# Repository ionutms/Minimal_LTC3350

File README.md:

# Minimal_LTC3350

## Overview

This repository contains a minimal KiCad design project for the Analog Devices LTC3350, a high-current supercapacitor backup controller and system monitor. The project includes schematic designs and PCB layout files for implementing this versatile backup power solution.

## Disclaimer

> [!NOTE]
> This project is provided "as is" and without any warranty, express or implied. For more details, please see the [LICENSE](LICENSE) file.

## About the LTC3350

The LTC3350 from Analog Devices is a high-current supercapacitor backup controller and system monitor designed for high-reliability backup power applications. It integrates a synchronous step-down/step-up controller that charges and monitors a series stack of 1–4 supercapacitors.

Key features include:

- **High-Efficiency Power Conversion:**
  - Synchronous step-down CC/CV charging for 1–4 series supercapacitors
  - Step-up mode in backup for greater utilization of stored energy
  - Supports 10A+ charge and backup currents
- **Advanced Monitoring:**
  - 14-bit ADC for monitoring system voltages and currents
  - Capacitance and ESR monitoring
  - I²C/SMBus interface for reading monitored parameters
- **Protection Features:**
  - Active overvoltage protection shunts
  - Internal active balancers (no external balance resistors needed)
  - Dual ideal diode PowerPath™ controller with N-channel MOSFETs
- **Programmable Current Limit:** Prioritizes system load over capacitor charge current
- **Wide Operating Range:**
  - Input Voltage (VIN): 4.5V to 35V
  - Capacitor Voltage (VCAP): Up to 5V per capacitor
- **Package:** Available in a 38-lead QFN package (5mm × 7mm × 0.75mm) with exposed pad
- **Automotive Qualified:** AEC-Q100 qualified for automotive applications

## Project Structure

```
minimal_ltc3350/
├── minimal_ltc3350.kicad_pro                     # Project configuration file
├── minimal_ltc3350.kicad_sch                     # Main schematic file
├── minimal_ltc3350.kicad_pcb                     # PCB layout file
├── fp-lib-table                                  # Footprint library table
├── sym-lib-table                                 # Symbol library table
├── docs/                                         # Documentation files
│   ├── bom/                                      # Bill of Materials
│   │   └── minimal_ltc3350_ibom.html             # Interactive BOM file
│   ├── pictures/                                 # Images and photos
│   │   ├── 1_minimal_ltc3350_side.png            # Side view of PCB
│   │   ├── 2_minimal_ltc3350_top.png             # Top view of PCB
│   │   └── 3_minimal_ltc3350_bottom.png          # Bottom view of PCB
│   └── schematics/                               # Schematic PDF exports
│       └── minimal_ltc3350_schematics.pdf        # Complete schematics PDF
└── KiCAD_Symbols_Generator/                      # Submodule for symbol generation from CSV data
```

## Project Features

This design provides a minimal implementation of the LTC3350 with:

- Proper power supply connections for 4.5V to 35V input range
- Supercapacitor stack configuration (1–4 series capacitors)
- Active balancing circuitry
- I²C/SMBus communication interface
- Current sensing and monitoring
- Standard footprint for the 38-lead QFN package

## Getting Started

### Prerequisites

- [KiCad EDA](https://www.kicad.org/) version 9.0 or later installed on your system
- Git (for cloning the repository and submodule management)

### Opening the Project

1. **Clone the repository** (including submodules):
   ```bash
   git clone --recursive https://github.com/ionutms/Minimal_LTC3350.git
   ```

   If you've already cloned the repository without submodules, initialize them with:
   ```bash
   git submodule init
   git submodule update
   ```

2. **Open the project in KiCad**:
   - Launch KiCad
   - Click "Open Existing Project"
   - Navigate to the cloned repository folder
   - Select the `minimal_ltc3350.kicad_pro` file

3. **Explore the design**:
   - Open the schematic editor to view the circuit design
   - Open the PCB editor to view the board layout
   - Review the symbol and footprint libraries used in the design

### Project Files

- **Main schematic**: `minimal_ltc3350.kicad_sch` - Contains the primary circuit design with the LTC3350 and support components
- **PCB layout**: `minimal_ltc3350.kicad_pcb` - Physical board design file with proper component placement
- **Project configuration**: `minimal_ltc3350.kicad_pro` - KiCad project settings

## Dependencies

This project has the following dependencies:

### 1. KiCAD Symbols Generator

This repository uses [KiCAD_Symbols_Generator](https://github.com/ionutms/KiCAD_Symbols_Generator) as a submodule for custom symbol generation.

To initialize the submodule after cloning this repository:

```bash
git submodule update --init --recursive
```

### 2. 3D Models

This project requires the [3D_Models_Vault](https://github.com/ionutms/3D_Models_Vault) repository for 3D models.

#### Setup for KiCAD 9:

1. Clone the 3D models repository:
   ```bash
   git clone https://github.com/ionutms/3D_Models_Vault.git
   ```

2. In KiCAD 9, add an environment variable:
   - Variable name: `KICAD9_3D_MODELS_VAULT`
   - Variable value: Full path to where you cloned the 3D_Models_Vault repository

## Usage

After setting up the dependencies, open the project in KiCad 9 to access all features including the 3D models.

## Symbol Generator Submodule

This project includes the KiCAD_Symbols_Generator as a submodule, which provides tools for generating KiCad symbols from CSV data files. For more information on using this tool, see the [KiCAD_Symbols_Generator documentation](minimal_ltc3350/KiCAD_Symbols_Generator/README.md).

## Documentation

The `docs` folder contains:
- Schematic PDF exports
- Images and photos of the design

## Visuals

The following images showcase the PCB design from different perspectives:

*Top View of the PCB*

*Bottom View of the PCB*

*Side View of the PCB*

*Left View of the PCB*

*Right View of the PCB*

*Front View of the PCB*

*Back View of the PCB*

## License

This project is licensed under the MIT License - see the [LICENSE](LICENSE) file for details.

## References

- [LTC3350 Datasheet](https://www.analog.com/media/en/technical-documentation/data-sheets/ltc3350.pdf)
- [LTC3350 Product Page](https://www.analog.com/en/products/ltc3350.html)
- [KiCad EDA](https://www.kicad.org/)

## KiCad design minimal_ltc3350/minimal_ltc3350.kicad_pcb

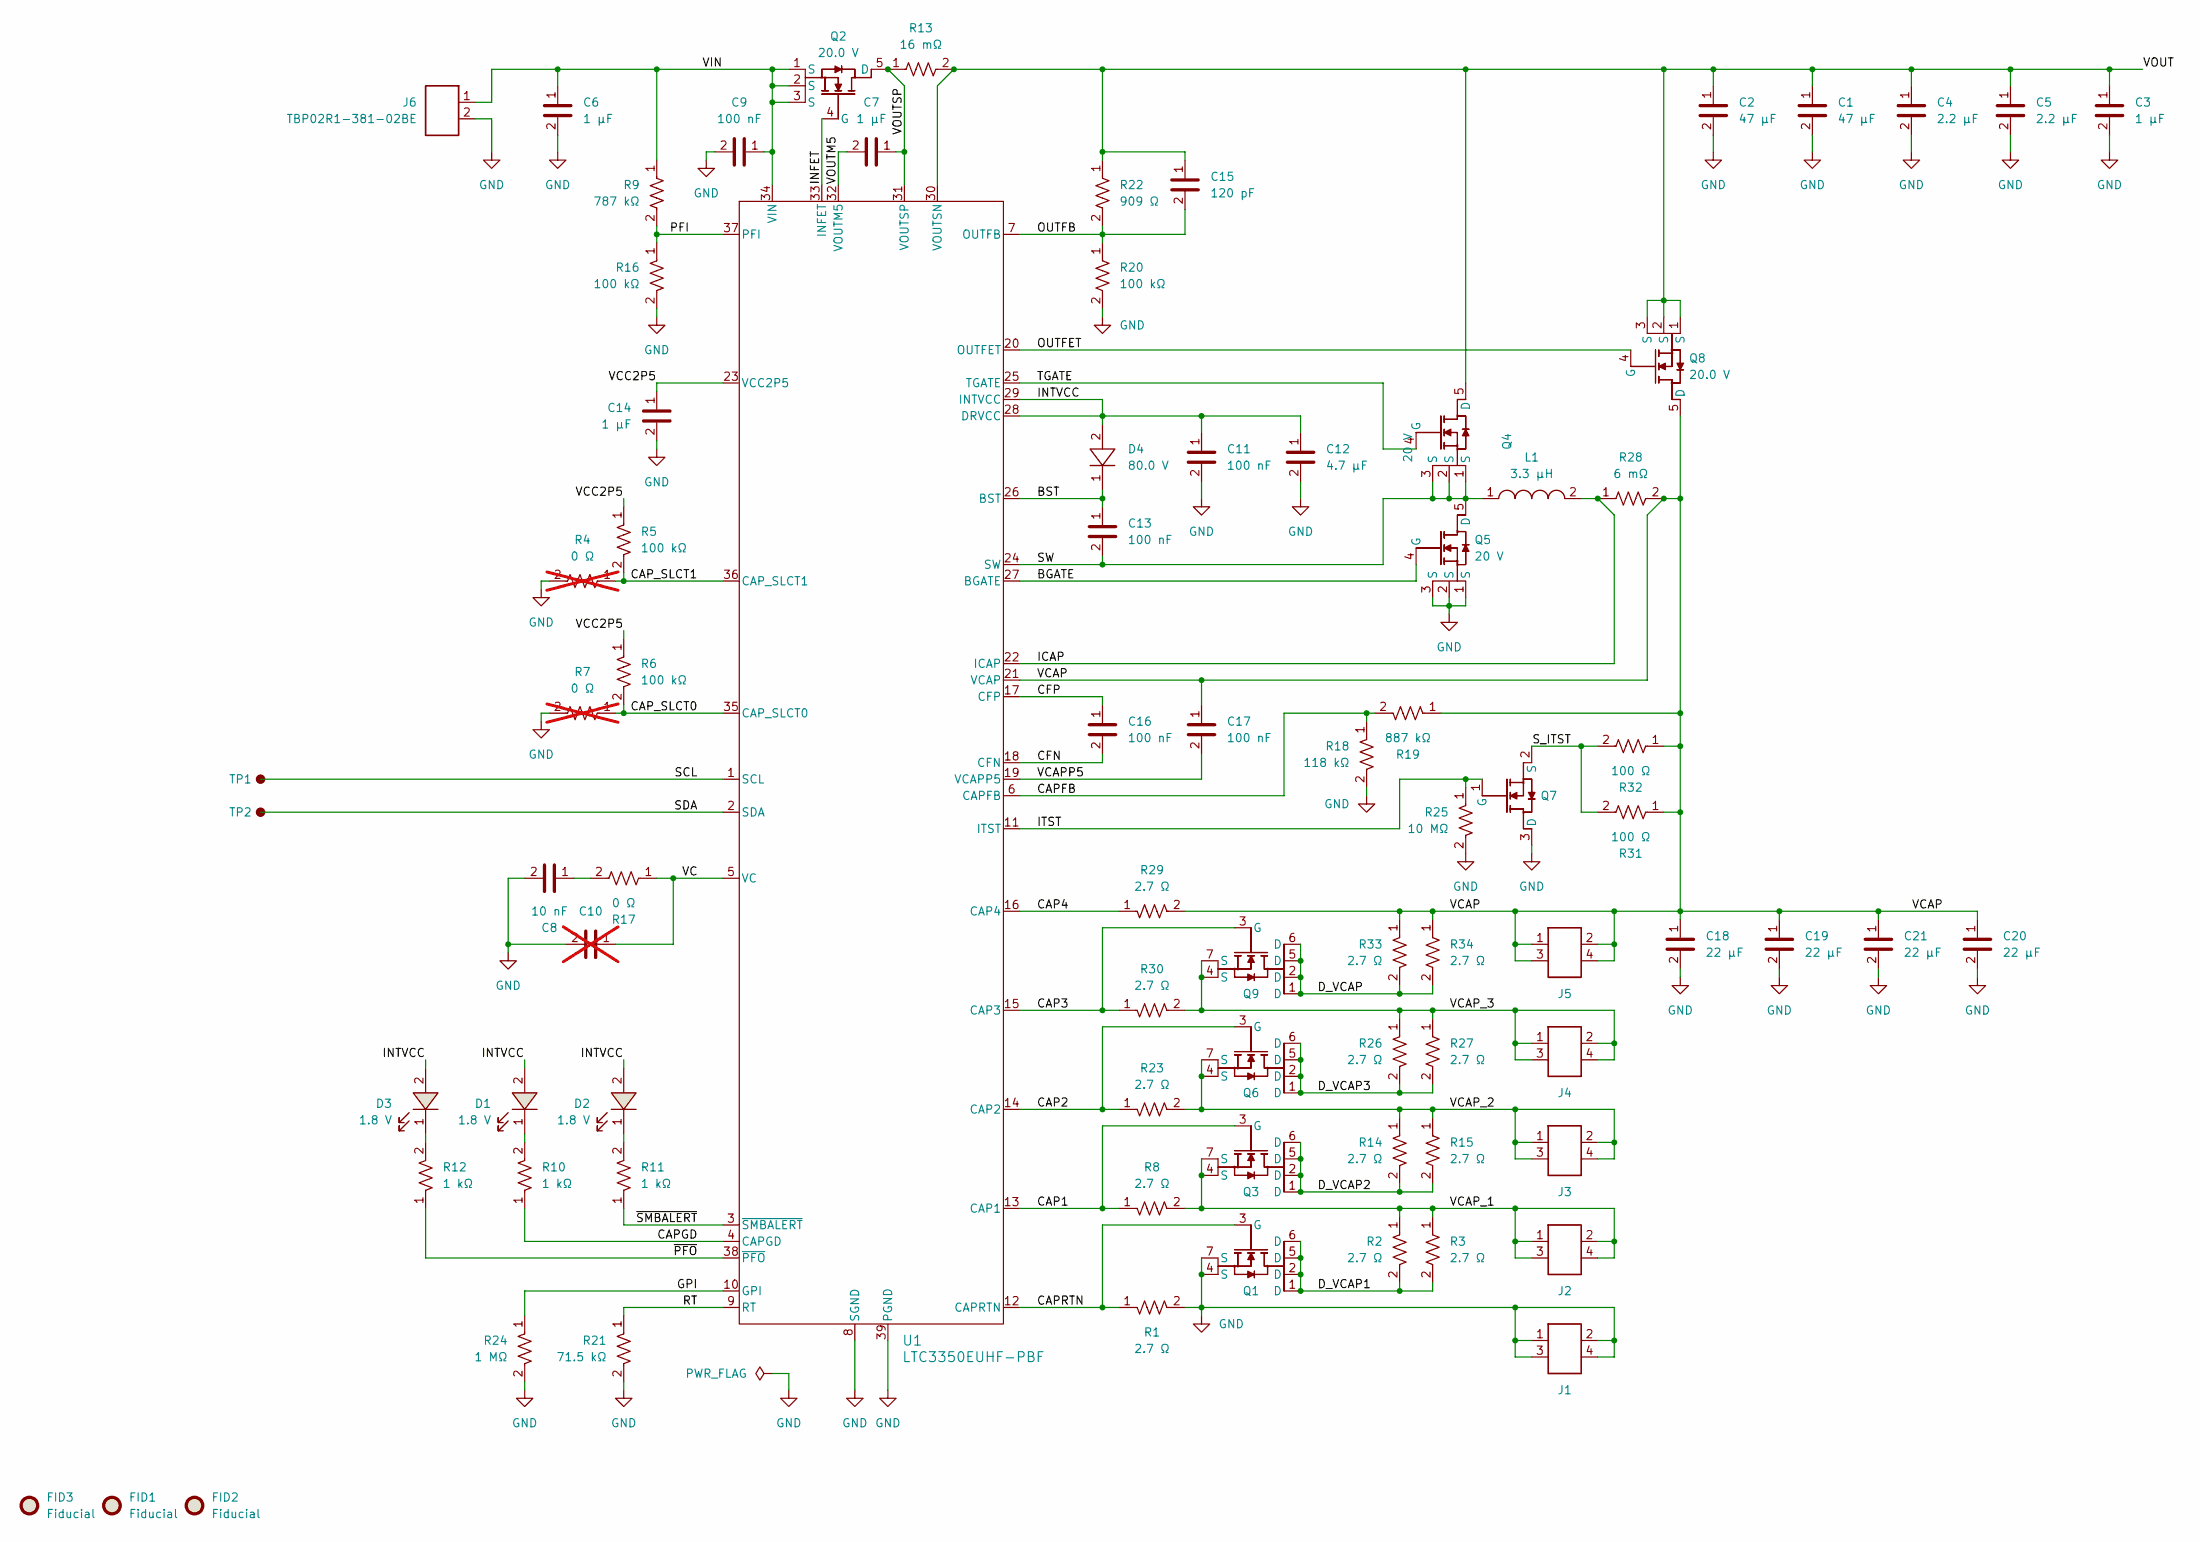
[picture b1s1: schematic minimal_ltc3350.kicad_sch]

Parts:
C1, C2: 47 µF; C_1206_3216Metric; Tolerance 20%; Voltage Rating 25V; MPN C3216X5R1E476M160AC
C3, C6, C7: 1 µF; C_0402_1005Metric; Tolerance 10%; Voltage Rating 25V; MPN C1005X5R1E105K050BC
C4, C5: 2.2 µF; C_0402_1005Metric; Tolerance 10%; Voltage Rating 25V; MPN C1005X5R1E225K050BC
C8: 10 nF; C_0402_1005Metric; Tolerance 10%; Voltage Rating 50V; MPN GCM155R71H103KA55D
C9, C11, C13, C16, C17: 100 nF; C_0402_1005Metric; Tolerance 10%; Voltage Rating 50V; MPN GCM155R71H104KE02D
C10: 10 nF; C_0402_1005Metric; Tolerance 10%; Voltage Rating 50V; MPN GCM155R71H103KA55D; not fitted
C12: 4.7 µF; C_0603_1608Metric; Tolerance 10%; Voltage Rating 10V; MPN GRM188C71A475KE11D
C14: 1 µF; C_0402_1005Metric; Tolerance 10%; Voltage Rating 16V; MPN C1005X6S1C105K050BC
C15: 120 pF; C_0402_1005Metric; Tolerance 1%; Voltage Rating 50V; MPN GCM1555C1H121FA16D
C18, C19, C20, C21: 22 µF; C_0805_2012Metric; Tolerance 20%; Voltage Rating 16V; MPN C2012X5R1C226M125AC
D1, D2, D3: 1.8 V; LED_RED_0402_1005Metric; MPN APHHS1005LSECK/J3-PF
D4: 80.0 V; SOD_523; MPN 1N4448HWT-7
FID1, FID2, FID3: Fiducial; Fiducial_0.5mm_Mask1mm
J1, J2, J3, J4, J5: CLP-102-02-G-D-BE; Current Rating (A) 5.2; Voltage Rating (V) 300; MPN CLP-102-02-G-D-BE
J6: TBP02R1-381-02BE; Current Rating (A) 8.0; Voltage Rating (V) 300; MPN TBP02R1-381-02BE
L1: 3.3 µH; XAL7030; Tolerance ±20%; MPN XAL7030-332ME
Q1, Q3, Q6, Q9: 8 V; PowerPAK SC-70; MPN SIA436DJ-T1-GE3
Q2, Q8: 20.0 V; PowerPAK 1212-8; MPN SIS438DN-T1-GE3
Q4, Q5: 20 V; TSDSON-8FL; MPN BSZ060NE2LS
Q7: 20.0 V; SOT23; MPN SI2374DS-T1-BE3
R1, R8, R23, R29, R30: 2.7 Ω; R_0805_2012Metric; Tolerance 1%; Voltage Rating 150V; MPN ERJ-6DQF2R7V
R2, R3, R14, R15, R26, R27, R33, R34: 2.7 Ω; R_2512_6332Metric; Tolerance 1%; Voltage Rating 200V; MPN RC2512FK-7W2R7L
R4, R7: 0 Ω; R_0402_1005Metric; Tolerance 5%; Voltage Rating 50V; MPN ERJ-2GE0R00X; not fitted
R5, R6, R16, R20: 100 kΩ; R_0402_1005Metric; Tolerance 1%; Voltage Rating 50V; MPN ERJ-2RKF1003X
R9: 787 kΩ; R_0402_1005Metric; Tolerance 1%; Voltage Rating 50V; MPN ERJ-2RKF7873X
R10, R11, R12: 1 kΩ; R_0402_1005Metric; Tolerance 1%; Voltage Rating 50V; MPN ERJ-2RKF1001X
R13: 16 mΩ; R_0612_1632Metric; Tolerance 1%; MPN ERJ-B2CFR016V
R17: 0 Ω; R_0402_1005Metric; Tolerance 5%; Voltage Rating 50V; MPN ERJ-2GE0R00X
R18: 118 kΩ; R_0402_1005Metric; Tolerance 1%; Voltage Rating 50V; MPN ERJ-2RKF1183X
R19: 887 kΩ; R_0402_1005Metric; Tolerance 1%; Voltage Rating 50V; MPN ERJ-2RKF8873X
R21: 71.5 kΩ; R_0402_1005Metric; Tolerance 1%; Voltage Rating 50V; MPN ERJ-2RKF7152X
R22: 909 Ω; R_0402_1005Metric; Tolerance 1%; Voltage Rating 50V; MPN ERJ-2RKF9090X
R24: 1 MΩ; R_0402_1005Metric; Tolerance 1%; Voltage Rating 50V; MPN ERJ-2RKF1004X
R25: 10 MΩ; R_0402_1005Metric; Tolerance 1%; Voltage Rating 50V; MPN RC0402FR-0710ML
R28: 6 mΩ; R_0612_1632Metric; Tolerance 1%; MPN WFCP06126L000FE66
R31, R32: 100 Ω; R_2512_6332Metric; Tolerance 1%; Voltage Rating 200V; MPN SR2512FK-7W100RL
TP1, TP2: TestPoint; TestPoint_THTPad_Castelated
U1: LTC3350EUHF-PBF; QFN-38_UHF_LIT; MPN LTC3350EUHF#PBF

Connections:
/BGATE: Q5.4 (G), U1.27 (BGATE)
/BST: C13.1, D4.1, U1.26 (BST)
/CAP1: Q3.3 (G), R8.1, U1.13 (CAP1)
/CAP2: Q6.3 (G), R23.1, U1.14 (CAP2)
/CAP3: Q9.3 (G), R30.1, U1.15 (CAP3)
/CAP4: R29.1, U1.16 (CAP4)
/CAPFB: R18.1, R19.2, U1.6 (CAPFB)
/CAPGD: R10.1, U1.4 (CAPGD)
/CAPRTN: Q1.3 (G), R1.1, U1.12 (CAPRTN)
/CAP_SLCT0: R6.2, R7.1, U1.35 (CAP_SLCT0)
/CAP_SLCT1: R4.1, R5.2, U1.36 (CAP_SLCT1)
/CFN: C16.2, U1.18 (CFN)
/CFP: C16.1, U1.17 (CFP)
/D_VCAP: Q9.1 (D), Q9.2 (D), Q9.5 (D), Q9.6 (D), R33.2, R34.2
/D_VCAP1: Q1.1 (D), Q1.2 (D), Q1.5 (D), Q1.6 (D), R2.2, R3.2
/D_VCAP2: Q3.1 (D), Q3.2 (D), Q3.5 (D), Q3.6 (D), R14.2, R15.2
/D_VCAP3: Q6.1 (D), Q6.2 (D), Q6.5 (D), Q6.6 (D), R26.2, R27.2
/GPI: R24.1, U1.10 (GPI)
/ICAP: L1.2, R28.1, U1.22 (ICAP)
/INFET: Q2.4 (G), U1.33 (INFET)
/INTVCC: C11.1, C12.1, D1.2, D2.2, D3.2, D4.2, U1.28 (DRVCC), U1.29 (INTVCC)
/ITST: Q7.1 (G), R25.1, U1.11 (ITST)
/OUTFB: C15.2, R20.1, R22.2, U1.7 (OUTFB)
/OUTFET: Q8.4 (G), U1.20 (OUTFET)
/PFI: R9.2, R16.1, U1.37 (PFI)
/RT: R21.1, U1.9 (RT)
/SCL: TP1.1, U1.1 (SCL)
/SDA: TP2.1, U1.2 (SDA)
/SW: C13.2, L1.1, Q4.1 (S), Q4.2 (S), Q4.3 (S), Q5.5 (D), U1.24 (SW)
/S_ITST: Q7.2 (S), R31.2, R32.2
/TGATE: Q4.4 (G), U1.25 (TGATE)
/VC: C10.1, R17.1, U1.5 (VC)
/VCAP: C17.1, C18.1, C19.1, C20.1, C21.1, J5.1, J5.2, J5.3, J5.4, Q8.5 (D), R19.1, R28.2, R29.2, R31.1, R32.1, R33.1, R34.1, U1.21 (VCAP)
/VCAPP5: C17.2, U1.19 (VCAPP5)
/VCAP_1: J2.1, J2.2, J2.3, J2.4, Q3.4 (S), Q3.7 (S), R2.1, R3.1, R8.2
/VCAP_2: J3.1, J3.2, J3.3, J3.4, Q6.4 (S), Q6.7 (S), R14.1, R15.1, R23.2
/VCAP_3: J4.1, J4.2, J4.3, J4.4, Q9.4 (S), Q9.7 (S), R26.1, R27.1, R30.2
/VCC2P5: C14.1, R5.1, R6.1, U1.23 (VCC2P5)
/VIN: C6.1, C9.1, J6.1, Q2.1 (S), Q2.2 (S), Q2.3 (S), R9.1, U1.34 (VIN)
/VOUT: C1.1, C2.1, C3.1, C4.1, C5.1, C15.1, Q4.5 (D), Q8.1 (S), Q8.2 (S), Q8.3 (S), R13.2, R22.1, U1.30 (VOUTSN)
/VOUTM5: C7.2, U1.32 (VOUTM5)
/VOUTSP: C7.1, Q2.5 (D), R13.1, U1.31 (VOUTSP)
/~PFO: R12.1, U1.38 (~PFO)
/~SMBALERT: R11.1, U1.3 (~SMBALERT)
GND: C1.2, C2.2, C3.2, C4.2, C5.2, C6.2, C8.2, C9.2, C10.2, C11.2, C12.2, C14.2, C18.2, C19.2, C20.2, C21.2, J1.1, J1.2, J1.3, J1.4, J6.2, Q1.4 (S), Q1.7 (S), Q5.1 (S), Q5.2 (S), Q5.3 (S), Q7.3 (D), R1.2, R4.2, R7.2, R16.2, R18.2, R20.2, R21.2, R24.2, R25.2, U1.8 (SGND), U1.39 (PGND)
unnamed: C8.1, R17.2
unnamed: D1.1, R10.2
unnamed: D2.1, R11.2
unnamed: D3.1, R12.2

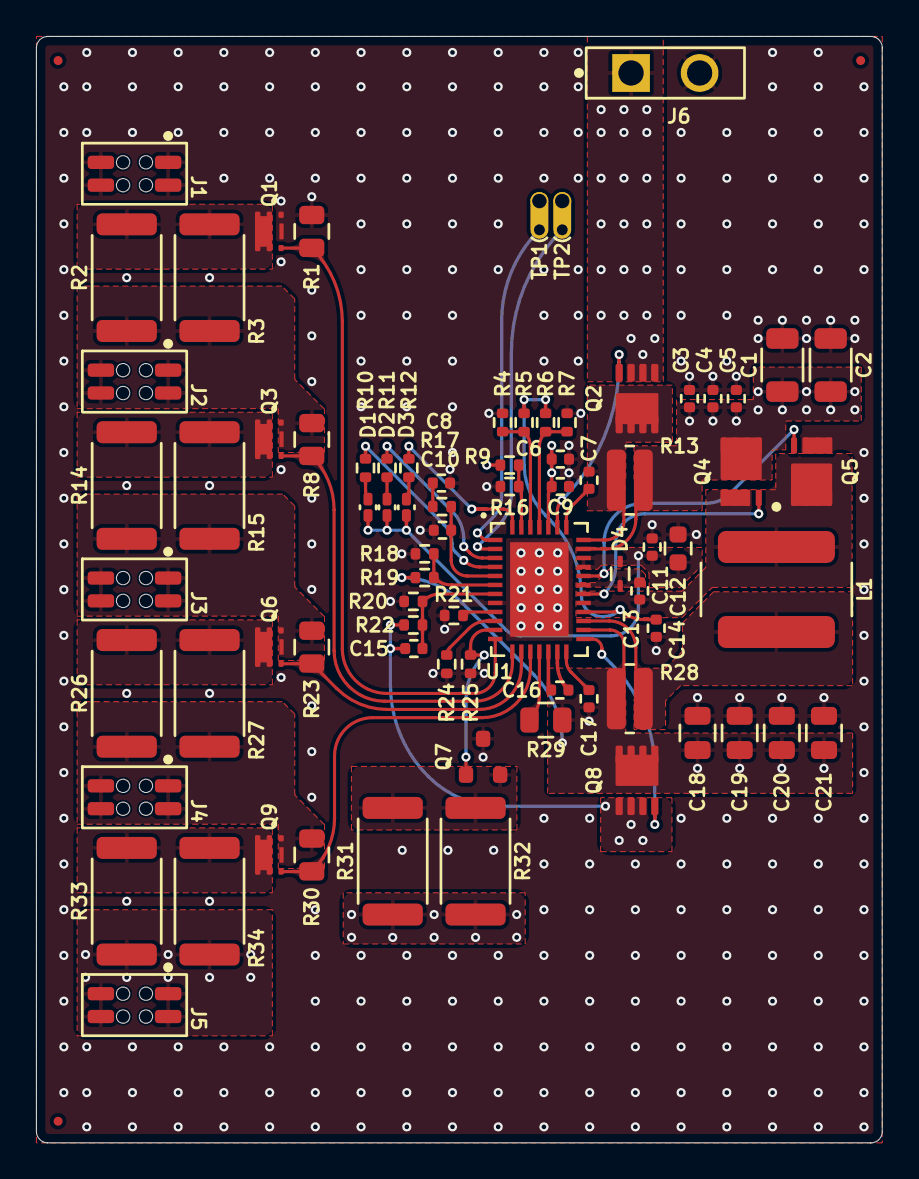
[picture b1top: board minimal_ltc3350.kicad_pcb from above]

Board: 4 copper layers, 47.0 x 61.5 mm, 81 parts (0 on the bottom side), 49 nets.

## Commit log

2025-12-01 Add KiCad project files for Minimal_LTC3350
2025-12-01 Add git submodules configuration and KiCAD Symbols Generator
2025-12-01 Add KiCad library table files (fp-lib-table and sym-lib-table)
2025-12-01 Update KiCad project files (PCB layout and project settings)
2025-12-01 chore: update workflows and kicad config from central repository
2025-12-01 Update KiCad documentation for minimal_ltc3350 (schematics and PCB renders)
2025-12-01 Update KiCad project files (PCB layout, project settings, and schematic)
2025-12-01 Update KiCad project files and submodule reference
2025-12-01 Add VOUT sensing resistor and update symbol libraries
2025-12-02 Update schematic and PCB with VOUT sensing resistor and component changes
2025-12-03 Update KiCad project: Component changes and layout improvements
2025-12-04 Update KiCad project: Component changes, net updates, and symbol library additions
2025-12-05 Update KiCad project files: PCB layout, schematic, project settings, and symbols generator
2025-12-06 Update KiCAD PCB and schematic files
2025-12-06 Add C19 capacitor and update component positions in KiCad project
2025-12-07 Update component positions and adjust properties in KiCad PCB design
2025-12-07 Update KiCAD PCB file
2025-12-07 Update KiCAD project files and symbols generator
2025-12-08 Update KiCad project: Add LED components and adjust resistor positions
2025-12-09 Update KiCad project: Update PCB layout and schematic
2025-12-11 Update KiCAD files and symbol table
2025-12-12 Update KiCAD symbols generator and schematic file
2025-12-13 Update KiCad project files: add new transistor components and connect nets
2025-12-14 Update KiCad project: PCB layout improvements and schematic changes
2025-12-21 Update KiCAD project files and symbol table
2025-12-21 Update capacitor symbols orientation and positioning in schematic
2025-12-21 backup
2025-12-21 Add Python project files and update .gitignore for Jupyter checkpoints
2025-12-22 Update KiCAD files: symbols generator, schematic, and PCB layout
2025-12-25 Update KiCad project files
2025-12-25 docs: update KiCad files
2025-12-25 Add numpy dependency to project
2025-12-25 Update LTC3350 Analysis notebook
2025-12-26 feat: Add requirements.txt for dependency management
2025-12-26 docs: Update LTC3350 Analysis notebook
2025-12-27 refactor: Improve UI of LTC3350 Interactive Calculator
2025-12-28 feat: Enhance LTC3350 analysis notebook
2025-12-29 feat: Update KiCad project and symbols
2025-12-29 Update files
2025-12-29 Update LTC3350 notebook: Add Roboto font, MathJax config, and adjust parameter labels
2025-12-30 Update KiCAD project files: Remove component properties and adjust zone connections
2025-12-31 Update KiCad schematic and PCB files
2026-01-01 Update KiCad project files: PCB layout, project settings, and schematic
2026-01-02 Update .gitignore and remove unnecessary files
2026-01-02 Update KiCAD Symbols Generator and PCB layout changes
2026-01-02 Update KiCAD project files: PCB and schematic
2026-01-03 Update KiCad project: Add supercap bank component and update net connections
2026-01-03 Update KiCAD config: adjust zoom factor and pan position
2026-01-11 wip: latest changes
2026-01-18 Update kicad-config.yml and remove unused test picture
2026-01-18 Update KiCAD configuration settings
2026-01-30 Update KiCad files
2026-03-04 Update README with comprehensive documentation
